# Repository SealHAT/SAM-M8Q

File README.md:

# SAM-M8Q
breakout board and libraries for SAM-M8 family GPS modules

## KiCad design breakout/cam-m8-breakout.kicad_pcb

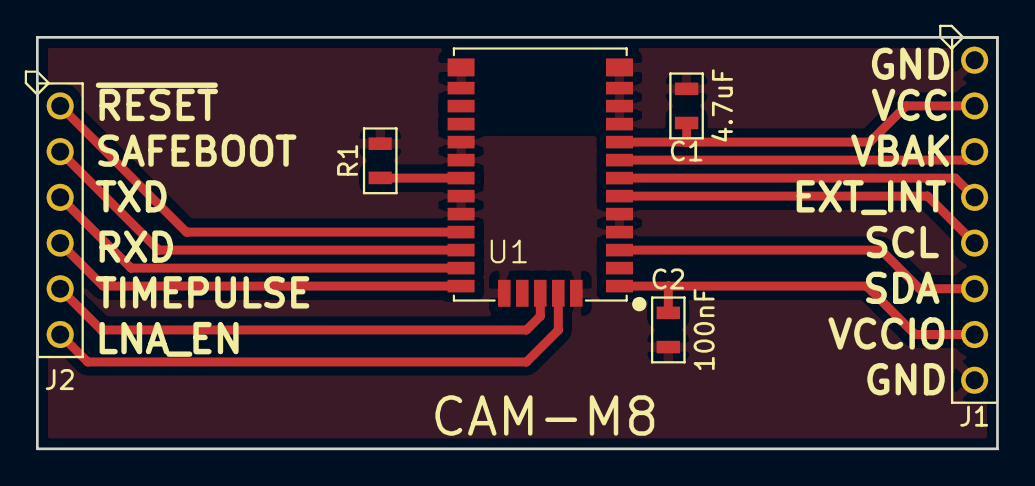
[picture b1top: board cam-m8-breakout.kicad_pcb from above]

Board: 2 copper layers, 53.3 x 22.9 mm, 6 parts (0 on the bottom side), 14 nets.

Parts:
C1: 4.7uF; MF_Passives-C0805
C2: 100nF; MF_Passives-C0805
J1: CON_01X08_PTH_2.54MM; MF_Connectors-PTH_2.54MM_01X08
J2: CON_01X06_PTH_2.54MM; MF_Connectors-PTH_2.54MM_01X06
R1: 0; MF_Passives-R0805
U1: CAM-M8; UBLOX_CAM-M8

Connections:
/EXT_INT: J1.4, U1.7
/LNA_EN: J2.6, U1.30
/RXD: J2.4, U1.26
/SAFEBOOT: J2.2, U1.24
/SCL: J1.5, U1.6
/SDA: J1.6, U1.3
/TIMEPULSE: J2.5, U1.29
/TXD: J2.3, U1.25
/VBAK: J1.3, U1.8
/VCCIO: C2.1, J1.7, U1.1
/~RESET: J2.1, U1.23
GND: C1.2, C2.2, J1.1, J1.8, R1.2, U1.4, U1.5, U1.10, U1.11, U1.12, U1.13, U1.14, U1.15, U1.18, U1.19, U1.21, U1.22, U1.27, U1.31
unnamed: R1.1, U1.20
VCC: C1.1, J1.2, U1.9

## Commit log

2018-01-22 created breakout folder and added ignores
2018-01-23 v1 of design and gerbers
2018-01-31 remove deprecated breakout files
2018-02-05 initial commit with empty header file and directory structure
2018-02-05 add dummy file to build folder structure
2018-02-05 added example project, ignroes, and moved files
2018-02-06 fixed bug in project and added link to header file for camm8
2018-02-06 changed directory structure and added ubx.h to project as a link
2018-02-06 made some types and formatting
2018-02-07 moved ubx to ubx header
2018-02-07 added ubx.c
2018-02-07 checksum function
2018-02-08 add some ubx class headers
2018-02-08 functions for NMEA checksum and testing
2018-02-10 added nmea_check function
2018-02-10 added minmea library
2018-02-10 converted project to working start file
2018-02-10 added ubx library
2018-02-12 removed endian header and created explicit define in ubx.c
2018-02-12 fixed missing line in minnmea.h
2018-02-12 no warning for minema
2018-02-12 fixed UBX lib errors
2018-02-12 renamed main headers and c file and updated project
2018-02-14 initial micro-to-gps api
2018-02-14 added time and location structs
2018-02-14 add profile enum and header fixes
2018-02-15 added nmea sentance completer function and restructred the check functions
2018-02-15 passing unit tests
2018-02-15 int2hex passing new unit test
2018-02-15 cleared out old files and added gps.c
2018-02-16 remove old test code
2018-02-19 moved custom protocols away, deprecated?
2018-02-20 fix ubx protos
2018-02-21 working on ubx set functions with demo
2018-02-21 change cfg_prt_spi to take cfg_prt struct
2018-02-21 clean up a bit
2018-02-21 added new config to enforce LF endings in source files
2018-02-21 added config to force source files to use LF endings
2018-02-21 merged in changes from nmea branch
2018-02-21 got rid of old files
2018-02-21 remove old example and add base ubx example project for xplained pro
2018-02-22 added feather project
2018-02-22 finish setcfg-prt function and built an spi config message
2018-02-23 align function for receiving, still fixing a bug
2018-02-24 abandoned align function, fix cfg_prt struct, rx weird message
2018-02-26 nav poll implemented and demonstrated
2018-02-26 forgot header for nav functions
2018-02-27 Update gps.h
    typo, copy of gps_sleep() should have been gps_wake()
2018-02-27 functionized config, still looking for ACK
2018-02-27 header for ubxnav messages
2018-02-28 small cleanup after testing
2018-02-28 getting configs, size works nice right now
2018-03-01 more get cfg tests
2018-03-06 clean up with more helper functions
2018-03-06 error check, move align to ubxutils, clean ups
2018-03-06 document align
2018-03-06 testing psmoo
2018-03-08 moved all code from main, implement gps_init and gps_getfix, need test
2018-03-08 fix alignUBXmessage to point pointer pointers to pointers
2018-03-09 update ubx timing
2018-03-09 add spi config function to gps init
2018-03-10 check prt config
2018-03-12 update error checking
2018-03-12 configured with usb
2018-03-12 update with usb-nonblock from SealHAT examples
2018-03-12 fixed usb undefine bug, turn on optimizations
2018-03-12 static inline
2018-03-13 output lat,lon formatted for gpsvisualizer
2018-03-13 functionize gpsusbxfer
2018-03-13 config timer for sampling
2018-03-14 implement polling for gps fix every 1s
2018-03-15 fix timing to 1s and add invalid fix value
2018-03-17 testing fix validity and accuracy, need cleanup
2018-04-02 fix a couple merge conflicts
2018-04-02 uptdate with timetest
2018-04-02 Configure AtmelStart with I2C driver
2018-04-03 start on i2c init function
2018-05-09 i2c write and i2c config
2018-05-10 Switched to and updated feather project, I2c testing
2018-05-10 Bring project up to date
2018-05-11 attempt to fix pins
2018-05-11 Moved over fresh project from SealHAT_example
2018-05-14 fixing up fifo and uart disable command
2018-05-15 disable uart bug, updating cfgprt to protocol v8
2018-05-16 Fix timing and missed packets error, working with cfgprt and txrready
2018-05-16 prepare messaging and better reads
2018-05-16 Watermark working fine
2018-05-16 remove dynamic ubx code
2018-05-17 remove deprecated code
2018-05-18 add fifo parsing
2018-05-18 update align
2018-05-18 update gps_selftest
2018-05-18 clean up for master pull
2018-05-21 remove extra buffers, add fifo count check
2018-05-21 fix check to return 32 signed
2018-05-21 Fix invalid gps logs and update log structs
2018-05-23 cleaned up your nasty repo
2018-05-24 Add a compile time switch for verbose nav messages
2018-05-25 add in power save mode config function
2018-05-26 update power saving mode functions to protocol v18
2018-05-26 add power mode settings functions
2018-05-27 power modes working and no infinite loops
2018-05-27 add clearing configs for fresh initialization
2018-05-28 make fifo static in gps.c
2018-05-30 Wrap power state functions to change rate and remove useless ubx libs
2018-05-31 fix msg and sample rates to same period
2018-06-01 Fix errors on config, add better config and verify funcs
2018-06-01 update search period
2018-06-02 enable power save
2018-06-02 Auto stash before merge of "master" and "origin/master"
    sleep, wake, and enablepsm functions all added
2018-06-04 add magic number satellite configuration function
2018-06-04 fix checksum for magic number
2018-06-04 extint working so well gps never wakes up...
2018-06-04 redid save, add extint timeout
2018-06-04 magic numbers for power save and better ack function
2018-06-04 magic number for cyclic tracking
2018-06-04 uncomment cfg
2018-06-05 add napping func
2018-06-06 much better ack and static (1s) msg rate
2018-06-06 no verify config and no reset in reconfig
2018-06-08 clear fifo before nmea
2018-06-10 moved public defines to seperate header to play nice with GUI
2018-06-12 update pxmreq in ubx libs to v18 and remove checks from config
2018-06-12 clean up sad reconfig function
2018-06-12 make fifo larger to account for acks from rxm-psmreq
